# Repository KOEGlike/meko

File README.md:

> [!CAUTION]
> V3 is a WIP, if you want updates follow my [journal](JOURNAL.md). Check out the [v2 branch](https://github.com/KOEGlike/meko/tree/v2) for a completed project

# Meko

A linux music player with ddr3, a 70hz e-paper display and a haptic touchpad

## Components

- **_MPU_**: SAMA7D65, it can boost up to 1GHz, good audio subsystem and gpu
- **_RAM_**: Half a gig of DDR3L(MT41K256M16TW)
- **_EPD_**: Sharp MIP LS022B7DH03, can go up to 70Hz, 240x320
- **_Audio_**: TAC5212 
  - **_DAC+AMP_**: 192kHz, 32-bit, 120dB SNR, 2Vrms
  - **_ADC_**: 192kHz, 32-bit, 119dB SNR
- **_Wireless_**: Bluetooth 6 with LE audio and WiFi 6E
- **_Touchpad_**: IQS7211E touch IC with DRV2605 haptic LRA driver
- **_USB_**: USB 2.0 with OTG

## Shoutouts

- Diamond Master from The KiCAD discord: Thank you for doing sims! Without you doing the impedance sim the project would have failed!
- Cyao: Thank you for taking a deep look at my DDR routing and pointing out a **BUNCH** of issues! The performance of my DDR would have been cooked without you!
- Daniel from The KiCAD discord: Thank you for helping me with all the high-speed basics, and pointing out issues with my DDR!
- r/PrintedCircuitBoard: Thank you for pointing out a bunch of small and large mistakes both in my schematic and PCB
- Hack Club: Thank you for providing an awesome community and funding for my project!!
- All the other people from the KiCAD Discord! Y'all are awesome!!

## Journals

Each versions has a detailed journal:

[V3 journal](JOURNAL.md)

[V2 journal](JOURNAL_OLD_V2.md)

[V1 journal](JOURNAL_OLD_V1.md)

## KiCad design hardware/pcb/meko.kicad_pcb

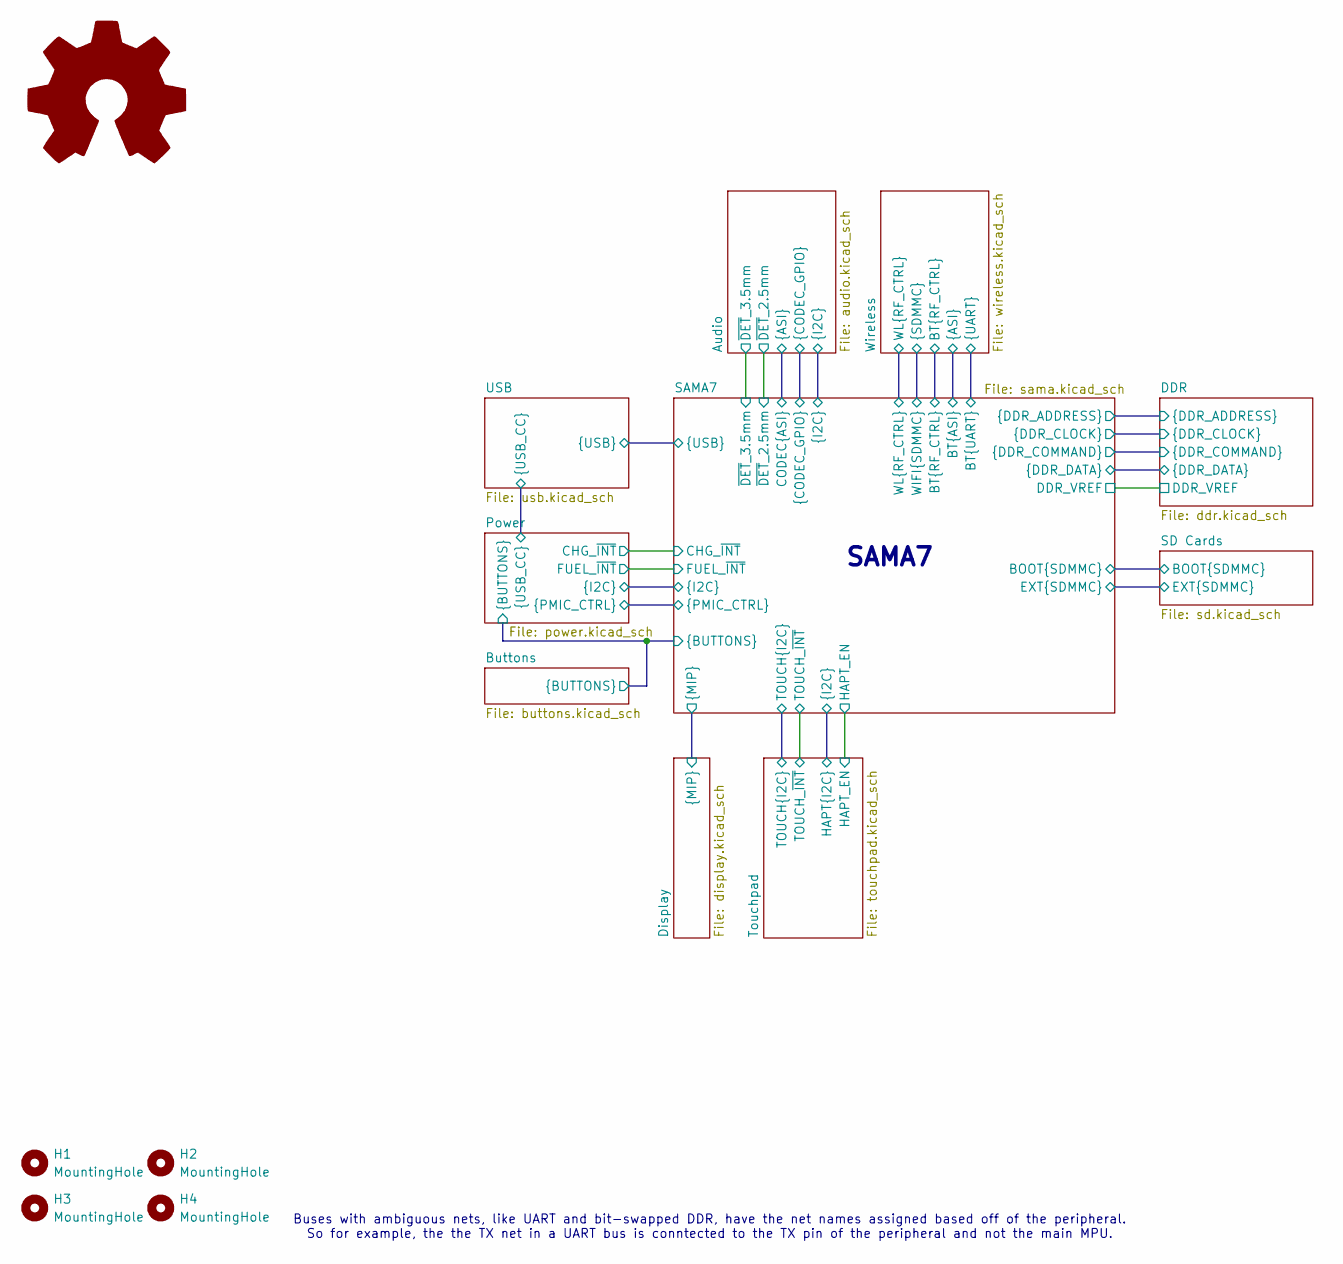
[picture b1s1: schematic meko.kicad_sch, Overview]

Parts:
H1, H2, H3, H4: MountingHole; MountingHole_2.2mm_M2
SYM1: Logo_Open_Hardware_Large; OSHW-Logo2_9.8x8mm_SilkScreen

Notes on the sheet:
Buses with ambiguous nets, like UART and bit-swapped DDR, have the net names assigned based off of the peripheral. So for example, the the TX net in a UART bus is conntected to the TX pin of the peripheral and not the main MPU.
SAMA7

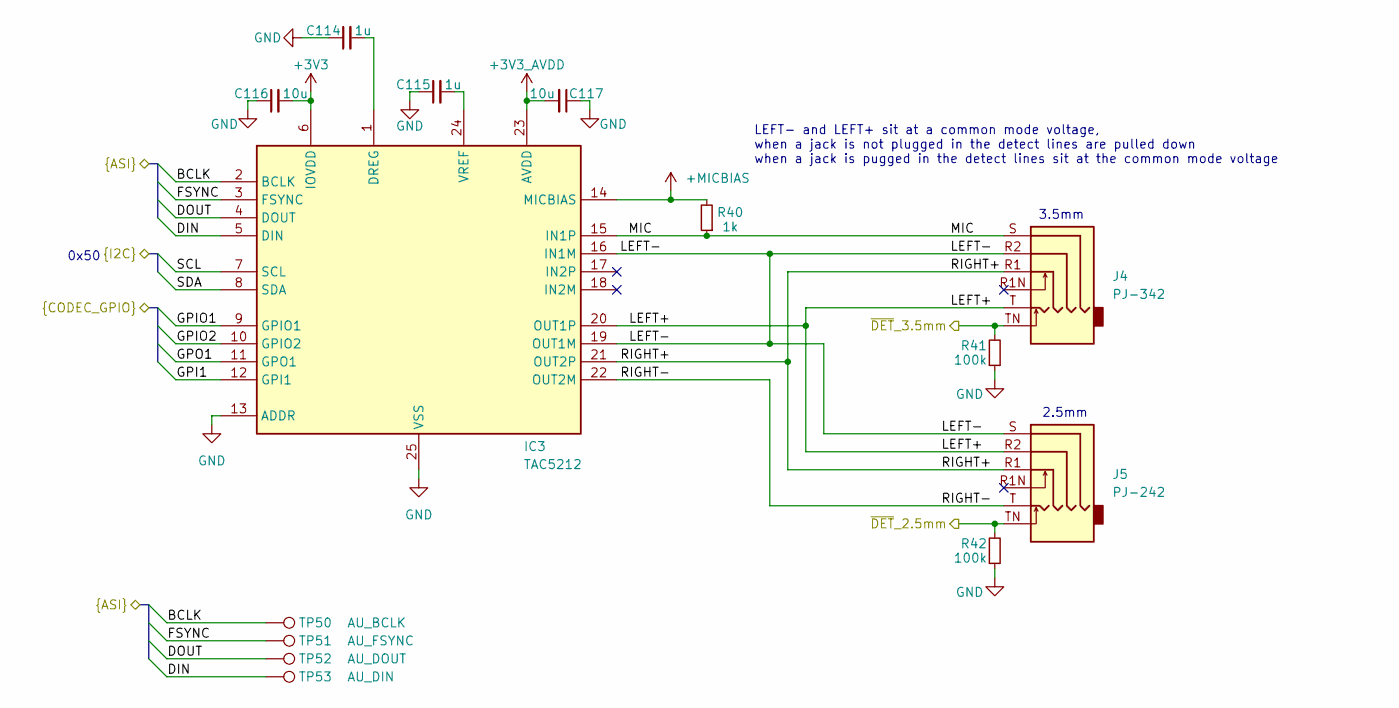
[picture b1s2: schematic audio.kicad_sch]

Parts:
C114, C115: 1u; C_0402_1005Metric
C116, C117: 10u; C_0402_1005Metric
IC3: TAC5212; VQFN-24-1EP_4x4mm_P0.5mm_EP2.45x2.45mm
J4: PJ-342; Jack_3.5mm_SHOUHAN_PJ-342; LCSC C668606
J5: PJ-242; Jack_2.5mm_PJ242_6P_12x6.2x4mm_Horizontal; LCSC C431536
R40: 1k; R_0402_1005Metric
R41, R42: 100k; R_0402_1005Metric
TP50: AU_BCLK; TestPoint_Pad_D1.0mm
TP51: AU_FSYNC; TestPoint_Pad_D1.0mm
TP52: AU_DOUT; TestPoint_Pad_D1.0mm
TP53: AU_DIN; TestPoint_Pad_D1.0mm

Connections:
+3V3: C116.2, IC3.6 (IOVDD); also elsewhere on the board
+3V3_AVDD: C117.2, IC3.23 (AVDD); also elsewhere on the board
+MICBIAS: IC3.14 (MICBIAS), R40.2
/Audio/BCLK: IC3.2 (BCLK), TP50.1 (1_1); also elsewhere on the board
/Audio/DIN: IC3.5 (DIN), TP53.1 (1_1); also elsewhere on the board
/Audio/DOUT: IC3.4 (DOUT), TP52.1 (1_1); also elsewhere on the board
/Audio/FSYNC: IC3.3 (FSYNC), TP51.1 (1_1); also elsewhere on the board
/Audio/GPI1: IC3.12 (GPI1); also elsewhere on the board
/Audio/GPIO1: IC3.9 (GPIO1); also elsewhere on the board
/Audio/GPIO2: IC3.10 (GPIO2); also elsewhere on the board
/Audio/GPO1: IC3.11 (GPO1); also elsewhere on the board
/Audio/LEFT+: IC3.20 (OUT1P), J4.T, J5.R2
/Audio/LEFT-: IC3.16 (IN1M), IC3.19 (OUT1M), J4.R2, J5.S
/Audio/MIC: IC3.15 (IN1P), J4.S, R40.1
/Audio/RIGHT+: IC3.21 (OUT2P), J4.R1, J5.R1
/Audio/RIGHT-: IC3.22 (OUT2M), J5.T
/Audio/SCL: IC3.7 (SCL); also elsewhere on the board
/Audio/SDA: IC3.8 (SDA); also elsewhere on the board
/Audio/~DET_2.5mm: J5.TN, R42.2; also elsewhere on the board
/Audio/~DET_3.5mm: J4.TN, R41.2; also elsewhere on the board
GND: C114.1, C115.1, C116.1, C117.1, IC3.13 (ADDR), IC3.25 (VSS), R41.1, R42.1; also elsewhere on the board
unnamed: C114.2, IC3.1 (DREG)
unnamed: C115.2, IC3.24 (VREF)

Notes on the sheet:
3.5mm
LEFT- and LEFT+ sit at a common mode voltage, when a jack is not plugged in the detect lines are pulled down when a jack is pugged in the detect lines sit at the common mode voltage
2.5mm
0x50

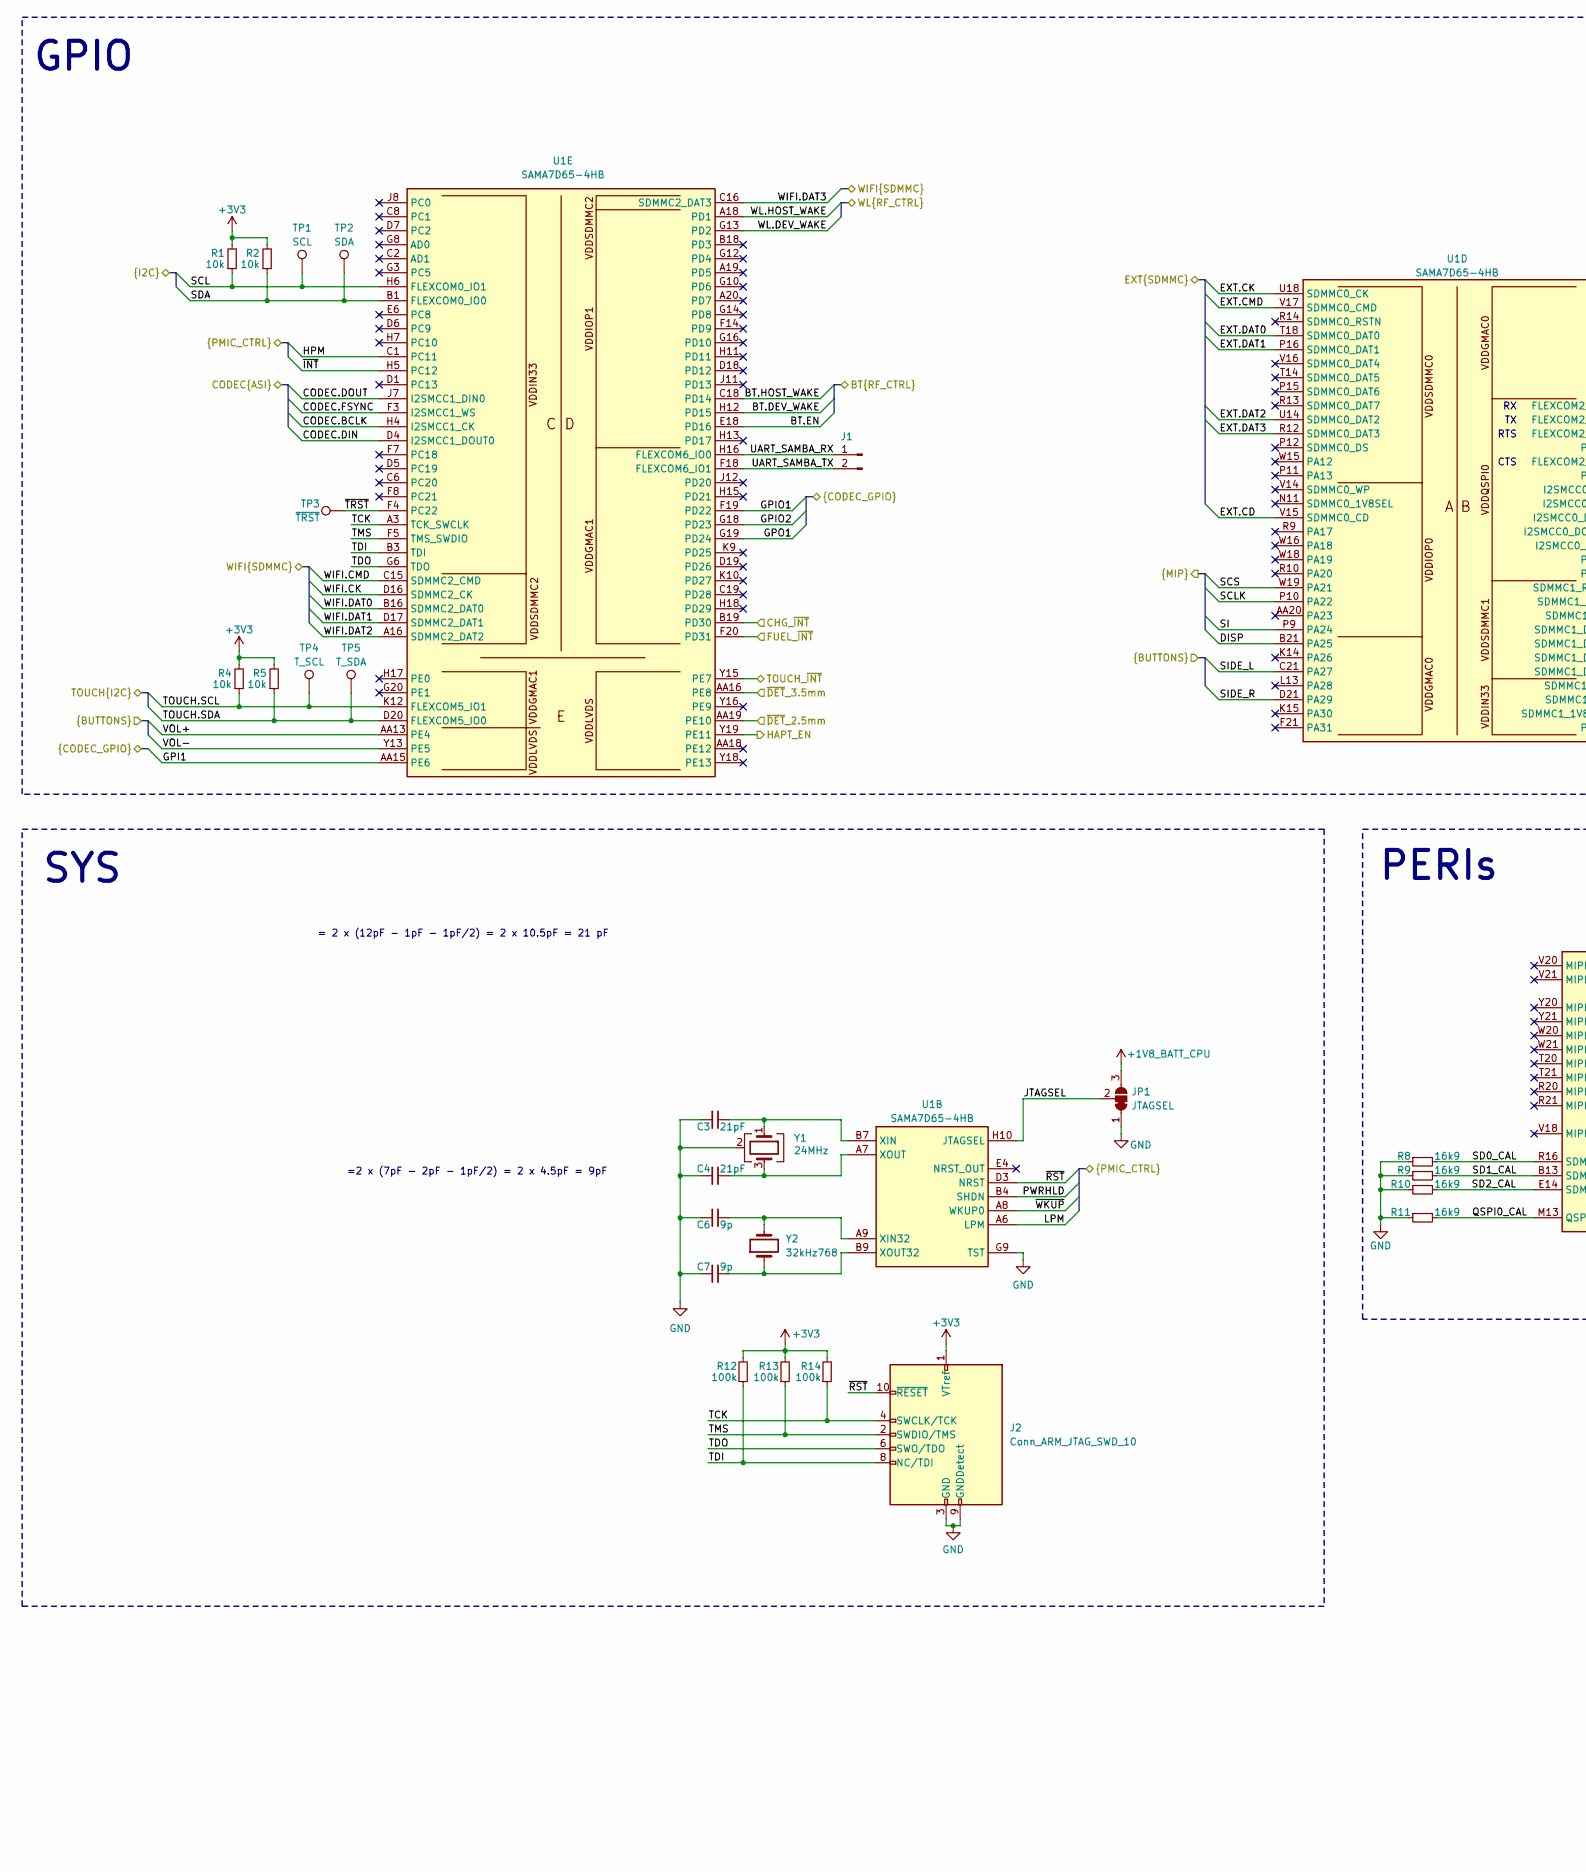
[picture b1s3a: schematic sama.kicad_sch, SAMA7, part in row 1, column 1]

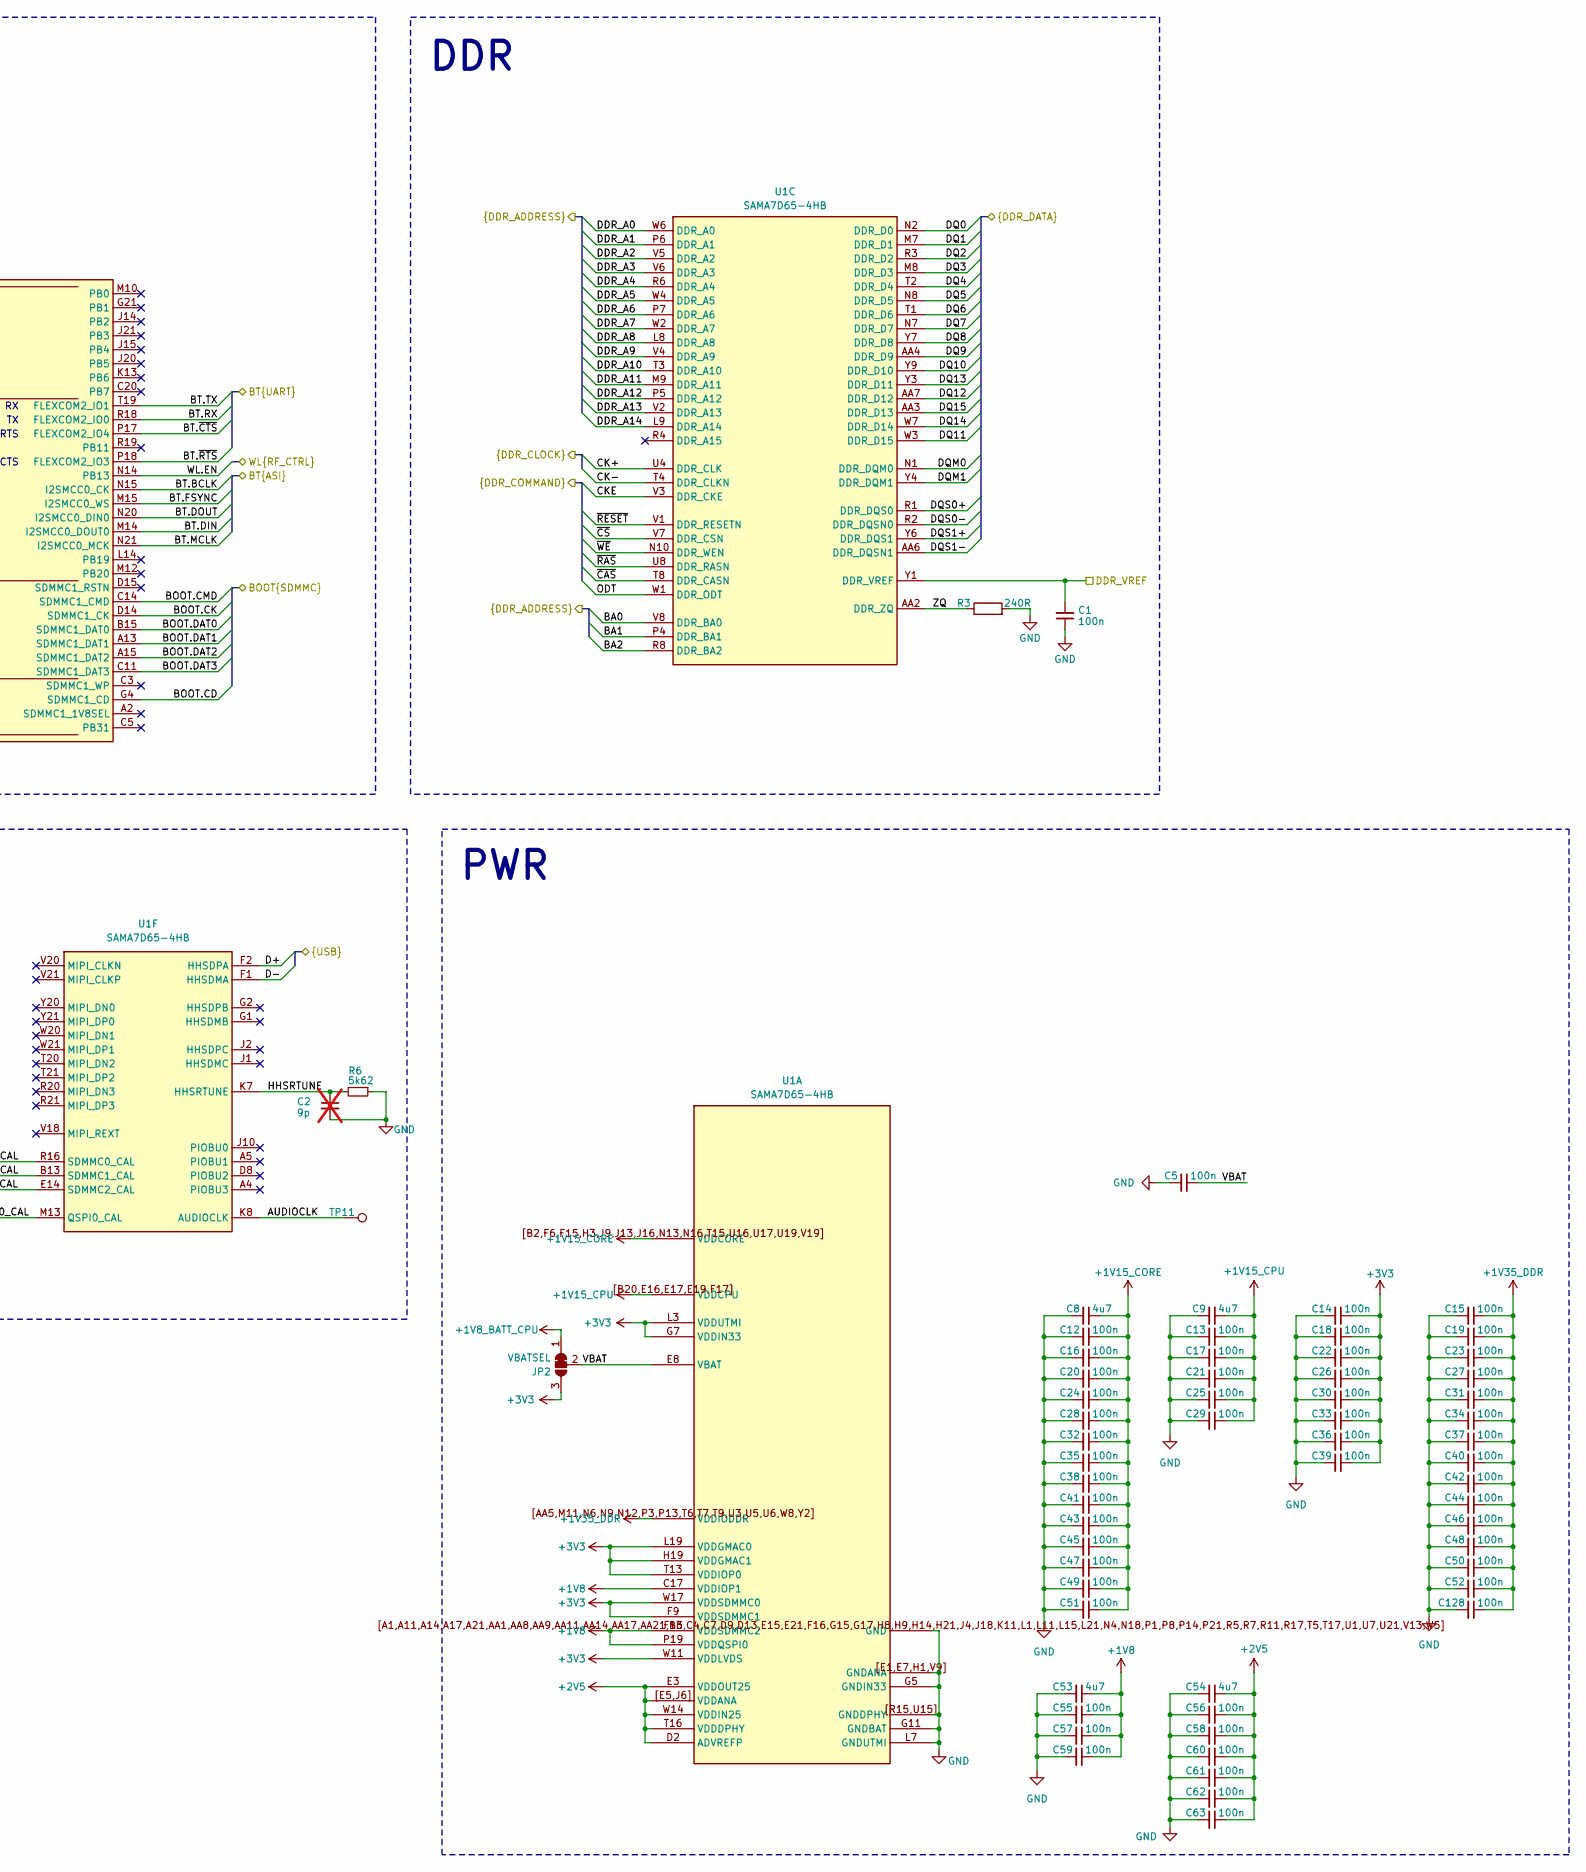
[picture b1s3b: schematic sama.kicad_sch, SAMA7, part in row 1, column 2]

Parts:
C1, C12, C15, C16, C18, C19, C20, C21, C22, C26, C28, C29, C30, C31, C39, C40, C43, C44, C46, C48, C51, C55, C56, C57, C59, C60, C62, C63, C128: 100n; C_0201_0603Metric
C2: 9p; C_0201_0603Metric; not fitted
C3, C4: 21pF; C_0201_0603Metric
C5, C13, C14, C17, C23, C24, C25, C27, C32, C33, C34, C35, C36, C37, C38, C41, C42, C45, C47, C49, C50, C52, C58, C61: 100n; C_0201_0603Metric_Dense
C6, C7: 9p; C_0201_0603Metric
C8, C9, C53, C54: 4u7; C_0402_1005Metric
J1: Conn_01x02_Pin; PinHeader_1x02_P2.54mm_Vertical
J2: Conn_ARM_JTAG_SWD_10; PinHeader_2x05_P1.27mm_Vertical
JP1: JTAGSEL; SolderJumper-3_P1.3mm_Bridged12_RoundedPad1.0x1.5mm
JP2: VBATSEL; SolderJumper-3_P1.3mm_Bridged12_RoundedPad1.0x1.5mm
R1, R2, R4, R5: 10k; R_0402_1005Metric
R3: 240R; R_0201_0603Metric
R6: 5k62; R_0201_0603Metric
R8, R9, R10, R11: 16k9; R_0201_0603Metric
R12, R13, R14: 100k; R_0402_1005Metric
TP1: SCL; TestPoint_Pad_D1.0mm
TP2: SDA; TestPoint_Pad_D1.0mm
TP3: ~{TRST}; TestPoint_Pad_D1.0mm
TP4: T_SCL; TestPoint_Pad_D1.0mm
TP5: T_SDA; TestPoint_Pad_D1.0mm
TP11: AUDIOCLK; TestPoint_Pad_D1.0mm
U1: SAMA7D65-4HB; Microchip_4HB_TFBGA-343_14x14mm_Layout21x21_P0.65mm
Y1: 24MHz; Crystal_SMD_3225-4Pin_3.2x2.5mm; MPN SX32Y024000BC1T001; LCSC C7420736
Y2: 32kHz768; Crystal_SMD_MicroCrystal_CC7V-T1A-2Pin_3.2x1.5mm; MPN SC-32S32.768kHz20PPM7pF

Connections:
+1V8: C53.1, C55.1, C57.1, C59.1, U1.C17 (VDDIOP1), U1.F13 (VDDSDMMC2), U1.P19 (VDDQSPI0); also elsewhere on the board
+1V8_BATT_CPU: JP1.3 (B), JP2.1 (A); also elsewhere on the board
+1V15_CORE: C8.1, C12.1, C16.1, C20.1, C24.1, C28.1, C32.1, C35.1, C38.1, C41.1, C43.1, C45.1, C47.1, C49.1, C51.1, U1.B2 (VDDCORE), U1.F6 (VDDCORE), U1.F15 (VDDCORE), U1.H3 (VDDCORE), U1.J9 (VDDCORE), U1.J13 (VDDCORE), U1.J16 (VDDCORE), U1.N13 (VDDCORE), U1.N16 (VDDCORE), U1.T15 (VDDCORE), U1.U16 (VDDCORE), U1.U17 (VDDCORE), U1.U19 (VDDCORE), U1.V19 (VDDCORE), U1.[B2,F6,F15,H3,J9,J1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 (VDDCORE); also elsewhere on the board
+1V15_CPU: C9.1, C13.1, C17.1, C21.1, C25.1, C29.1, U1.B20 (VDDCPU), U1.E16 (VDDCPU), U1.E17 (VDDCPU), U1.E19 (VDDCPU), U1.F17 (VDDCPU), U1.[B20,E16,E17,E19,F1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 (VDDCPU); also elsewhere on the board
+1V35_DDR: C15.1, C19.1, C23.1, C27.1, C31.1, C34.1, C37.1, C40.1, C42.1, C44.1, C46.1, C48.1, C50.1, C52.1, C128.1, U1.AA5 (VDDIODDR), U1.M11 (VDDIODDR), U1.N6 (VDDIODDR), U1.N9 (VDDIODDR), U1.N12 (VDDIODDR), U1.P3 (VDDIODDR), U1.P13 (VDDIODDR), U1.T6 (VDDIODDR), U1.T7 (VDDIODDR), U1.T9 (VDDIODDR), U1.U3 (VDDIODDR), U1.U5 (VDDIODDR), U1.U6 (VDDIODDR), U1.W8 (VDDIODDR), U1.Y2 (VDDIODDR), U1.[AA5,M11,N6,N9,N12,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 (VDDIODDR); also elsewhere on the board
+2V5: C54.1, C56.1, C58.1, C60.1, C61.1, C62.1, C63.1, U1.D2 (ADVREFP), U1.E3 (VDDOUT25), U1.E5 (VDDANA), U1.J6 (VDDANA), U1.T16 (VDDDPHY), U1.W14 (VDDIN25), U1.[E5,J6] (VDDANA)
+3V3: C14.1, C18.1, C22.1, C26.1, C30.1, C33.1, C36.1, C39.1, J2.1 (VTref), JP2.3 (B), R1.2, R2.2, R4.2, R5.2, R12.2, R13.2, R14.2, U1.F9 (VDDSDMMC1), U1.G7 (VDDIN33), U1.H19 (VDDGMAC1), U1.L3 (VDDUTMI), U1.L19 (VDDGMAC0), U1.T13 (VDDIOP0), U1.W11 (VDDLVDS), U1.W17 (VDDSDMMC0); also elsewhere on the board
/Audio/BCLK: U1.H4 (I2SMCC1_CK); also elsewhere on the board
/Audio/DIN: U1.D4 (I2SMCC1_DOUT0); also elsewhere on the board
/Audio/DOUT: U1.J7 (I2SMCC1_DIN0); also elsewhere on the board
/Audio/FSYNC: U1.F3 (I2SMCC1_WS); also elsewhere on the board
/Audio/GPI1: U1.AA15 (PE6); also elsewhere on the board
/Audio/GPIO1: U1.F19 (PD22); also elsewhere on the board
/Audio/GPIO2: U1.G18 (PD23); also elsewhere on the board
/Audio/GPO1: U1.G19 (PD24); also elsewhere on the board
/Audio/SCL: R1.1, TP1.1 (1_1), U1.H6 (FLEXCOM0_IO1); also elsewhere on the board
/Audio/SDA: R2.1, TP2.1 (1_1), U1.B1 (FLEXCOM0_IO0); also elsewhere on the board
/Audio/~DET_2.5mm: U1.AA19 (PE10); also elsewhere on the board
/Audio/~DET_3.5mm: U1.AA16 (PE8); also elsewhere on the board
/Buttons/SIDE_L: U1.C21 (PA27); also elsewhere on the board
/Buttons/SIDE_R: U1.D21 (PA29); also elsewhere on the board
/Buttons/VOL+: U1.AA13 (PE4); also elsewhere on the board
/Buttons/VOL-: U1.Y13 (PE5); also elsewhere on the board
/DDR/BA0: U1.V8 (DDR_BA0); also elsewhere on the board
/DDR/BA1: U1.P4 (DDR_BA1); also elsewhere on the board
/DDR/BA2: U1.R8 (DDR_BA2); also elsewhere on the board
/DDR/CK+: U1.U4 (DDR_CLK); also elsewhere on the board
/DDR/CK-: U1.T4 (DDR_CLKN); also elsewhere on the board
/DDR/CKE: U1.V3 (DDR_CKE); also elsewhere on the board
/DDR/DDR_A0: U1.W6 (DDR_A0); also elsewhere on the board
/DDR/DDR_A1: U1.P6 (DDR_A1); also elsewhere on the board
/DDR/DDR_A2: U1.V5 (DDR_A2); also elsewhere on the board
/DDR/DDR_A3: U1.V6 (DDR_A3); also elsewhere on the board
/DDR/DDR_A4: U1.R6 (DDR_A4); also elsewhere on the board
/DDR/DDR_A5: U1.W4 (DDR_A5); also elsewhere on the board
/DDR/DDR_A6: U1.P7 (DDR_A6); also elsewhere on the board
/DDR/DDR_A7: U1.W2 (DDR_A7); also elsewhere on the board
/DDR/DDR_A8: U1.L8 (DDR_A8); also elsewhere on the board
/DDR/DDR_A9: U1.V4 (DDR_A9); also elsewhere on the board
/DDR/DDR_A10: U1.T3 (DDR_A10); also elsewhere on the board
/DDR/DDR_A11: U1.M9 (DDR_A11); also elsewhere on the board
/DDR/DDR_A12: U1.P5 (DDR_A12); also elsewhere on the board
/DDR/DDR_A13: U1.V2 (DDR_A13); also elsewhere on the board
/DDR/DDR_A14: U1.L9 (DDR_A14); also elsewhere on the board
/DDR/DDR_VREF: C1.2, U1.Y1 (DDR_VREF); also elsewhere on the board
/DDR/DQ0: U1.N2 (DDR_D0); also elsewhere on the board
/DDR/DQ1: U1.M7 (DDR_D1); also elsewhere on the board
/DDR/DQ2: U1.R3 (DDR_D2); also elsewhere on the board
/DDR/DQ3: U1.M8 (DDR_D3); also elsewhere on the board
/DDR/DQ4: U1.T2 (DDR_D4); also elsewhere on the board
/DDR/DQ5: U1.N8 (DDR_D5); also elsewhere on the board
/DDR/DQ6: U1.T1 (DDR_D6); also elsewhere on the board
/DDR/DQ7: U1.N7 (DDR_D7); also elsewhere on the board
/DDR/DQ8: U1.Y7 (DDR_D8); also elsewhere on the board
/DDR/DQ9: U1.AA4 (DDR_D9); also elsewhere on the board
/DDR/DQ10: U1.Y9 (DDR_D10); also elsewhere on the board
/DDR/DQ11: U1.W3 (DDR_D15); also elsewhere on the board
/DDR/DQ12: U1.AA7 (DDR_D12); also elsewhere on the board
/DDR/DQ13: U1.Y3 (DDR_D11); also elsewhere on the board
/DDR/DQ14: U1.W7 (DDR_D14); also elsewhere on the board
/DDR/DQ15: U1.AA3 (DDR_D13); also elsewhere on the board
/DDR/DQM0: U1.N1 (DDR_DQM0); also elsewhere on the board
/DDR/DQM1: U1.Y4 (DDR_DQM1); also elsewhere on the board
/DDR/DQS0+: U1.R1 (DDR_DQS0); also elsewhere on the board
/DDR/DQS0-: U1.R2 (DDR_DQSN0); also elsewhere on the board
/DDR/DQS1+: U1.Y6 (DDR_DQS1); also elsewhere on the board
/DDR/DQS1-: U1.AA6 (DDR_DQSN1); also elsewhere on the board
/DDR/ODT: U1.W1 (DDR_ODT); also elsewhere on the board
/DDR/~CAS: U1.T8 (DDR_CASN); also elsewhere on the board
/DDR/~CS: U1.V7 (DDR_CSN); also elsewhere on the board
/DDR/~RAS: U1.U8 (DDR_RASN); also elsewhere on the board
/DDR/~RESET: U1.V1 (DDR_RESETN); also elsewhere on the board
/DDR/~WE: U1.N10 (DDR_WEN); also elsewhere on the board
/Display/DISP: U1.B21 (PA25); also elsewhere on the board
/Display/SCLK: U1.P10 (PA22); also elsewhere on the board
/Display/SCS: U1.W19 (PA21); also elsewhere on the board
/Display/SI: U1.P9 (PA24); also elsewhere on the board
/Power/CHG_~INT: U1.B19 (PD30); also elsewhere on the board
/Power/FUEL_~INT: U1.F20 (PD31); also elsewhere on the board
/Power/HPM: U1.C1 (PC11); also elsewhere on the board
/Power/LPM: U1.A6 (LPM); also elsewhere on the board
/Power/PWRHLD: U1.B4 (SHDN); also elsewhere on the board
/Power/~INT: U1.H5 (PC12); also elsewhere on the board
/Power/~RST: J2.10 (~RESET), U1.D3 (NRST); also elsewhere on the board
/Power/~WKUP: U1.A8 (WKUP0); also elsewhere on the board
/SAMA7/AUDIOCLK: TP11.1 (1_1), U1.K8 (AUDIOCLK)
/SAMA7/BOOT.CD: U1.G4 (SDMMC1_CD); also elsewhere on the board
/SAMA7/BOOT.CK: U1.D14 (SDMMC1_CK); also elsewhere on the board
/SAMA7/BOOT.CMD: U1.C14 (SDMMC1_CMD); also elsewhere on the board
/SAMA7/BOOT.DAT0: U1.B15 (SDMMC1_DAT0); also elsewhere on the board
/SAMA7/BOOT.DAT1: U1.A13 (SDMMC1_DAT1); also elsewhere on the board
/SAMA7/BOOT.DAT2: U1.A15 (SDMMC1_DAT2); also elsewhere on the board
/SAMA7/BOOT.DAT3: U1.C11 (SDMMC1_DAT3); also elsewhere on the board
/SAMA7/BT.BCLK: U1.N15 (I2SMCC0_CK); also elsewhere on the board
/SAMA7/BT.DEV_WAKE: U1.H12 (PD15); also elsewhere on the board
/SAMA7/BT.DIN: U1.M14 (I2SMCC0_DOUT0); also elsewhere on the board
/SAMA7/BT.DOUT: U1.N20 (I2SMCC0_DIN0); also elsewhere on the board
/SAMA7/BT.EN: U1.E18 (PD16); also elsewhere on the board
/SAMA7/BT.FSYNC: U1.M15 (I2SMCC0_WS); also elsewhere on the board
/SAMA7/BT.HOST_WAKE: U1.C18 (PD14); also elsewhere on the board
/SAMA7/BT.MCLK: U1.N21 (I2SMCC0_MCK); also elsewhere on the board
/SAMA7/BT.RX: U1.R18 (FLEXCOM2_IO0); also elsewhere on the board
/SAMA7/BT.TX: U1.T19 (FLEXCOM2_IO1); also elsewhere on the board
/SAMA7/BT.~CTS: U1.P17 (FLEXCOM2_IO4); also elsewhere on the board
/SAMA7/BT.~RTS: U1.P18 (FLEXCOM2_IO3); also elsewhere on the board
/SAMA7/D+: U1.F2 (HHSDPA); also elsewhere on the board
/SAMA7/D-: U1.F1 (HHSDMA); also elsewhere on the board
/SAMA7/EXT.CD: U1.V15 (SDMMC0_CD); also elsewhere on the board
/SAMA7/EXT.CK: U1.U18 (SDMMC0_CK); also elsewhere on the board
/SAMA7/EXT.CMD: U1.V17 (SDMMC0_CMD); also elsewhere on the board
/SAMA7/EXT.DAT0: U1.T18 (SDMMC0_DAT0); also elsewhere on the board
/SAMA7/EXT.DAT1: U1.P16 (SDMMC0_DAT1); also elsewhere on the board
/SAMA7/EXT.DAT2: U1.U14 (SDMMC0_DAT2); also elsewhere on the board
/SAMA7/EXT.DAT3: U1.R12 (SDMMC0_DAT3); also elsewhere on the board
/SAMA7/HAPT_EN: U1.Y19 (PE11); also elsewhere on the board
/SAMA7/HHSRTUNE: C2.1, R6.2, U1.K7 (HHSRTUNE)
/SAMA7/JTAGSEL: JP1.2 (C), U1.H10 (JTAGSEL)
/SAMA7/QSPI0_CAL: R11.2, U1.M13 (QSPI0_CAL)
/SAMA7/SD0_CAL: R8.2, U1.R16 (SDMMC0_CAL)
/SAMA7/SD1_CAL: R9.2, U1.B13 (SDMMC1_CAL)
/SAMA7/SD2_CAL: R10.2, U1.E14 (SDMMC2_CAL)
/SAMA7/TCK: J2.4 (SWCLK/TCK), R14.1, U1.A3 (TCK_SWCLK)
/SAMA7/TDI: J2.8 (NC/TDI), R12.1, U1.B3 (TDI)
/SAMA7/TDO: J2.6 (SWO/TDO), U1.G6 (TDO)
/SAMA7/TMS: J2.2 (SWDIO/TMS), R13.1, U1.F5 (TMS_SWDIO)
/SAMA7/TOUCH.SCL: R4.1, TP4.1 (1_1), U1.K12 (FLEXCOM5_IO1); also elsewhere on the board
/SAMA7/TOUCH.SDA: R5.1, TP5.1 (1_1), U1.D20 (FLEXCOM5_IO0); also elsewhere on the board
/SAMA7/TOUCH_~INT: U1.Y15 (PE7); also elsewhere on the board
/SAMA7/UART_SAMBA_RX: J1.1, U1.H16 (FLEXCOM6_IO0)
/SAMA7/UART_SAMBA_TX: J1.2, U1.F18 (FLEXCOM6_IO1)
/SAMA7/VBAT: C5.1, JP2.2 (C), U1.E8 (VBAT)
/SAMA7/WIFI.CK: U1.D16 (SDMMC2_CK); also elsewhere on the board
/SAMA7/WIFI.CMD: U1.C15 (SDMMC2_CMD); also elsewhere on the board
/SAMA7/WIFI.DAT0: U1.B16 (SDMMC2_DAT0); also elsewhere on the board
/SAMA7/WIFI.DAT1: U1.D17 (SDMMC2_DAT1); also elsewhere on the board
/SAMA7/WIFI.DAT2: U1.A16 (SDMMC2_DAT2); also elsewhere on the board
/SAMA7/WIFI.DAT3: U1.C16 (SDMMC2_DAT3); also elsewhere on the board
/SAMA7/WL.DEV_WAKE: U1.G13 (PD2); also elsewhere on the board
/SAMA7/WL.EN: U1.N14 (PB13); also elsewhere on the board
/SAMA7/WL.HOST_WAKE: U1.A18 (PD1); also elsewhere on the board
/SAMA7/ZQ: R3.1, U1.AA2 (DDR_ZQ)
/SAMA7/~TRST: TP3.1 (1_1), U1.F4 (PC22)
GND: C1.1, C2.2, C3.2, C4.2, C5.2, C6.2, C7.2, C8.2, C9.2, C12.2, C13.2, C14.2, C15.2, C16.2, C17.2, C18.2, C19.2, C20.2, C21.2, C22.2, C23.2, C24.2, C25.2, C26.2, C27.2, C28.2, C29.2, C30.2, C31.2, C32.2, C33.2, C34.2, C35.2, C36.2, C37.2, C38.2, C39.2, C40.2, C41.2, C42.2, C43.2, C44.2, C45.2, C46.2, C47.2, C48.2, C49.2, C50.2, C51.2, C52.2, C53.2, C54.2, C55.2, C56.2, C57.2, C58.2, C59.2, C60.2, C61.2, C62.2, C63.2, C128.2, J2.3 (GND), J2.5 (GND), J2.9 (GNDDetect), JP1.1 (A), R3.2, R6.1, R8.1, R9.1, R10.1, R11.1, U1.A1 (GND), U1.A11 (GND), U1.A14 (GND), U1.A17 (GND), U1.A21 (GND), U1.AA1 (GND), U1.AA8 (GND), U1.AA9 (GND), U1.AA11 (GND), U1.AA14 (GND), U1.AA17 (GND), U1.AA21 (GND), U1.B6 (GND), U1.C4 (GND), U1.C7 (GND), U1.D9 (GND), U1.D13 (GND), U1.E1 (GNDANA), U1.E7 (GNDANA), U1.E15 (GND), U1.E21 (GND), U1.F16 (GND), U1.G5 (GNDIN33), U1.G9 (TST), U1.G11 (GNDBAT), U1.G15 (GND), U1.G17 (GND), U1.H1 (GNDANA), U1.H8 (GND), U1.H9 (GND), U1.H14 (GND), U1.H21 (GND), U1.J4 (GND), U1.J18 (GND), U1.K11 (GND), U1.L1 (GND), U1.L7 (GNDUTMI), U1.L11 (GND), U1.L15 (GND), U1.L21 (GND), U1.N4 (GND), U1.N18 (GND), U1.P1 (GND), U1.P8 (GND), U1.P14 (GND), U1.P21 (GND), U1.R5 (GND), U1.R7 (GND), U1.R11 (GND), U1.R15 (GNDDPHY), U1.R17 (GND), U1.T5 (GND), U1.T17 (GND), U1.U1 (GND), U1.U7 (GND), U1.U15 (GNDDPHY), U1.U21 (GND), U1.V9 (GNDANA), U1.V13 (GND), U1.W5 (GND), U1.[A1,A11,A14,A17,A21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 (GND), U1.[E1,E7,H1,V9] (GNDANA), U1.[R15,U15] (GNDDPHY), Y1.2 (G), Y1.4 (G); also elsewhere on the board
unnamed: C6.1, U1.A9 (XIN32), Y2.2
unnamed: C3.1, U1.B7 (XIN), Y1.1
unnamed: C7.1, U1.B9 (XOUT32), Y2.1
unnamed: C4.1, U1.A7 (XOUT), Y1.3

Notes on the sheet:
PERIs
GPIO
=2 x (7pF - 2pF - 1pF/2) = 2 x 4.5pF = 9pF
= 2 x (12pF - 1pF - 1pF/2) = 2 x 10.5pF = 21 pF
SYS
PWR
DDR
CTS
RTS

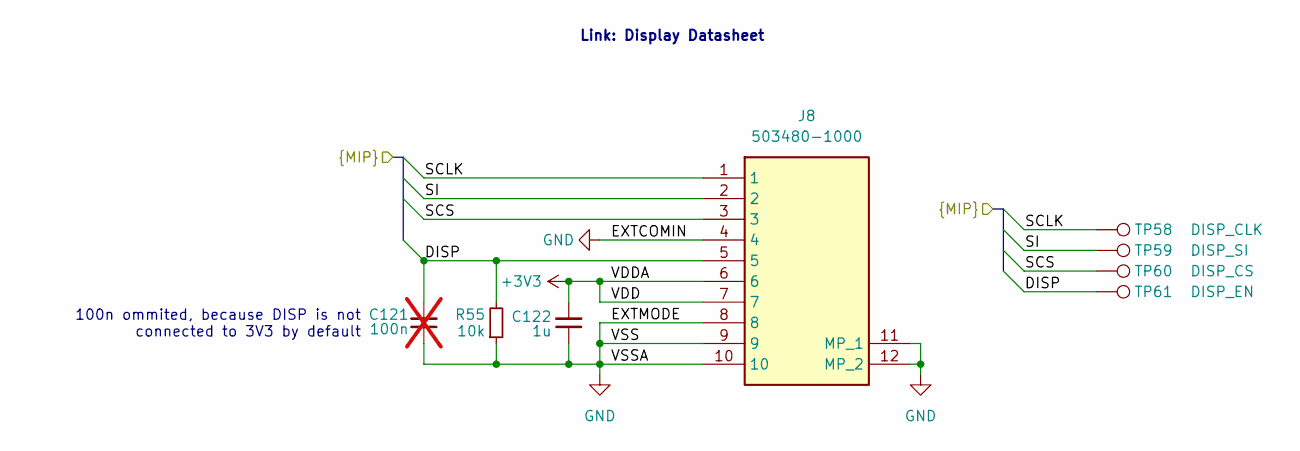
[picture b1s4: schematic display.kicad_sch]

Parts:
C121: 100n; C_0201_0603Metric; not fitted
C122: 1u; C_0402_1005Metric
J8: 503480-1000; 5034801000; MPN 503480-1000; LCSC C127355
R55: 10k; R_0402_1005Metric
TP58: DISP_CLK; TestPoint_Pad_D1.0mm
TP59: DISP_SI; TestPoint_Pad_D1.0mm
TP60: DISP_CS; TestPoint_Pad_D1.0mm
TP61: DISP_EN; TestPoint_Pad_D1.0mm

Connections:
+3V3: C122.2, J8.6, J8.7; also elsewhere on the board
/Display/DISP: C121.2, J8.5, R55.2, TP61.1 (1_1); also elsewhere on the board
/Display/SCLK: J8.1, TP58.1 (1_1); also elsewhere on the board
/Display/SCS: J8.3, TP60.1 (1_1); also elsewhere on the board
/Display/SI: J8.2, TP59.1 (1_1); also elsewhere on the board
GND: C121.1, C122.1, J8.4, J8.8, J8.9, J8.10, J8.11 (MP_1), J8.12 (MP_2), R55.1; also elsewhere on the board

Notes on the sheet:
100n ommited, because DISP is not connected to 3V3 by default
Link: Display Datasheet

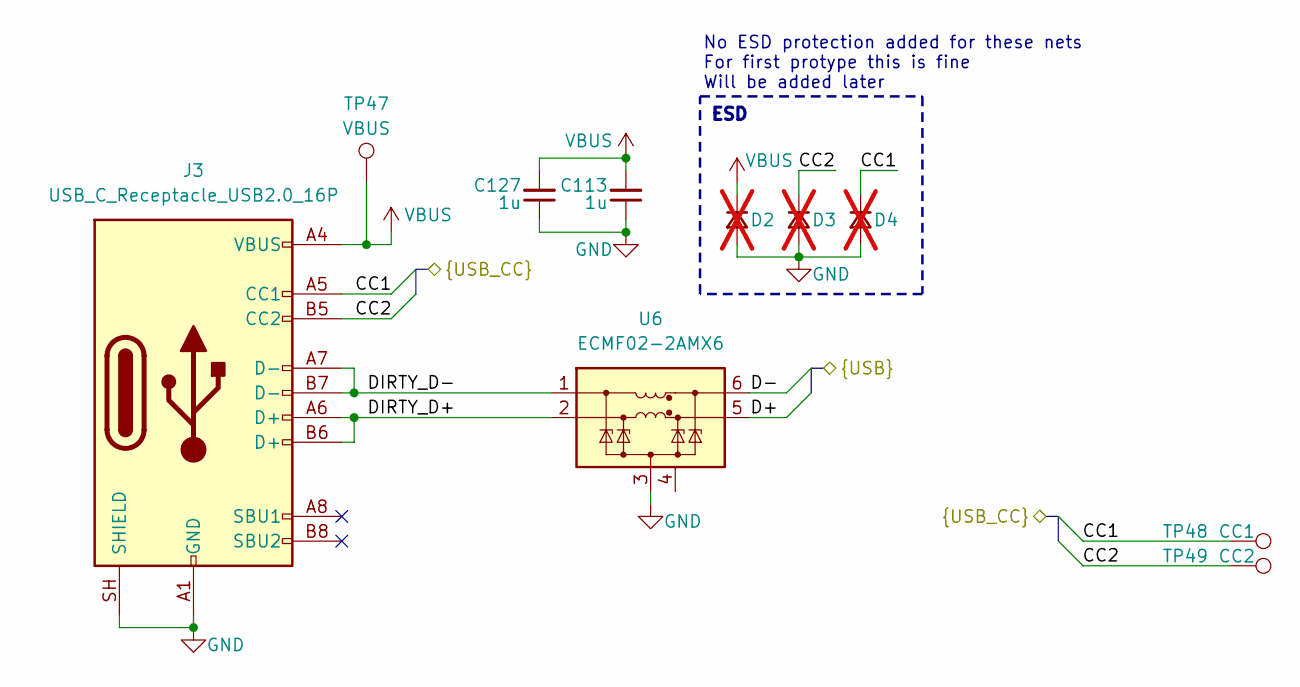
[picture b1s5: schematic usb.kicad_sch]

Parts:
C113, C127: 1u; C_0402_1005Metric
D2, D3, D4: ESD441; ESD441DPLR; not fitted
J3: USB_C_Receptacle_USB2.0_16P; USB_C_Receptacle_HRO_TYPE-C-31-M-12
TP47: VBUS; TestPoint_Pad_D1.0mm
TP48: CC1; TestPoint_Pad_D1.0mm
TP49: CC2; TestPoint_Pad_D1.0mm
U6: ECMF02-2AMX6; ST_UQFN-6L_1.5x1.7mm_P0.5mm

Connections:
/Power/CC1: D4.1 (K), J3.A5 (CC1), TP48.1 (1_1); also elsewhere on the board
/Power/CC2: D3.1 (K), J3.B5 (CC2), TP49.1 (1_1); also elsewhere on the board
/SAMA7/D+: U6.5 (D-_out); also elsewhere on the board
/SAMA7/D-: U6.6 (D+_out); also elsewhere on the board
/USB/DIRTY_D+: J3.A6 (D+), J3.B6 (D+), U6.2 (D-_in)
/USB/DIRTY_D-: J3.A7 (D-), J3.B7 (D-), U6.1 (D+_in)
GND: C113.1, C127.1, D2.2 (A), D3.2 (A), D4.2 (A), J3.A1 (GND), J3.A12 (GND), J3.B1 (GND), J3.B12 (GND), J3.SH (SHIELD), U6.3 (GND); also elsewhere on the board
VBUS: C113.2, C127.2, D2.1 (K), J3.A4 (VBUS), J3.A9 (VBUS), J3.B4 (VBUS), J3.B9 (VBUS), TP47.1 (1_1); also elsewhere on the board

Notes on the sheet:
No ESD protection added for these nets For first protype this is fine Will be added later
ESD

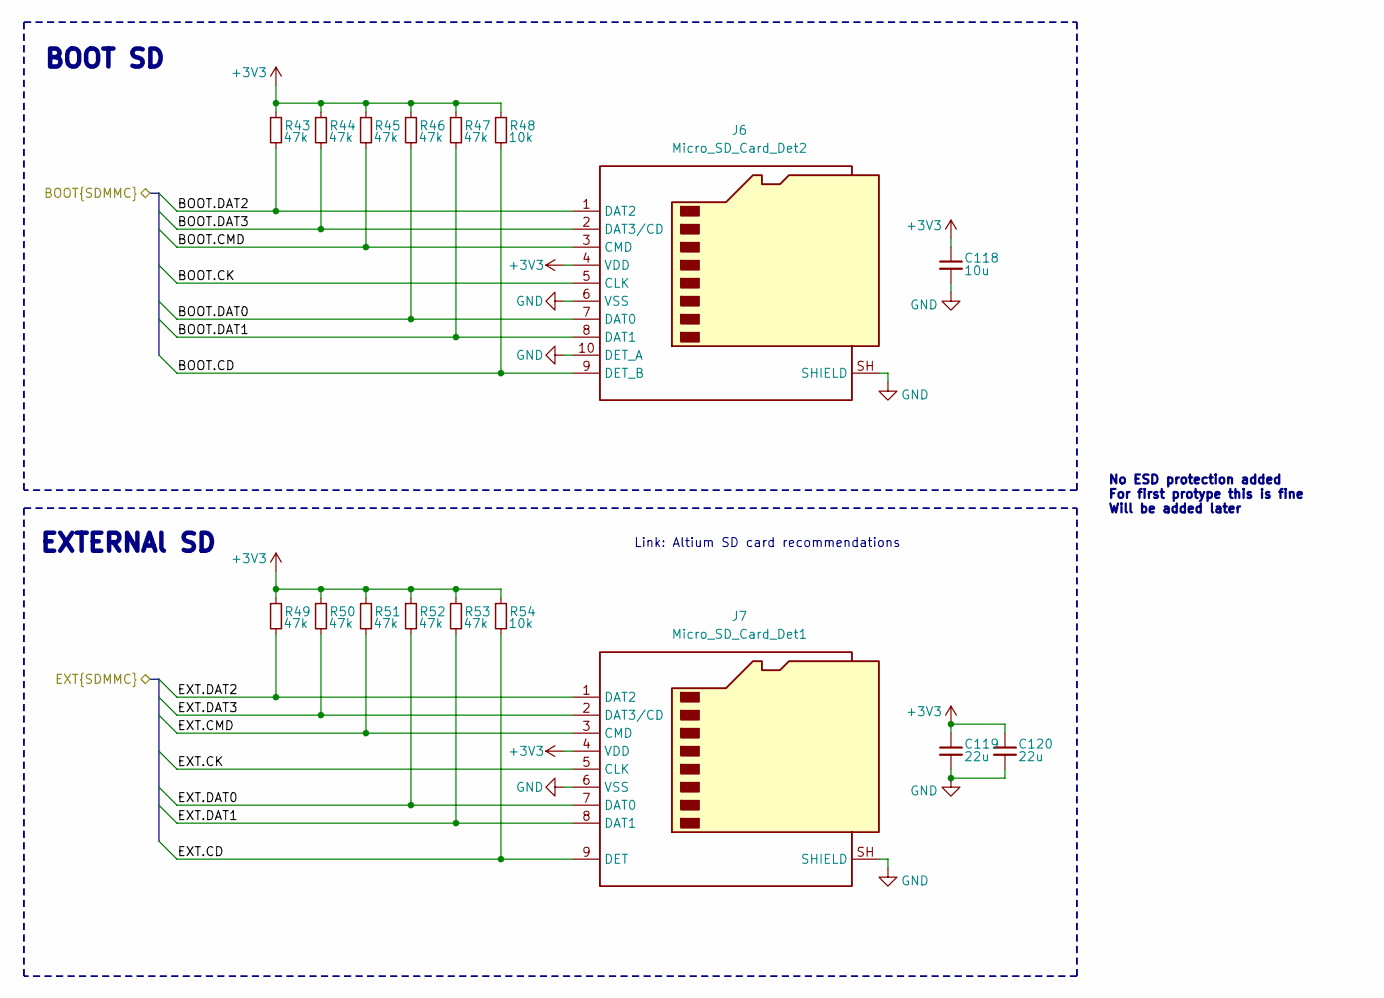
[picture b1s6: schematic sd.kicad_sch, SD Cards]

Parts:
C118: 10u; C_0402_1005Metric
C119, C120: 22u; C_0603_1608Metric
J6: Micro_SD_Card_Det2; microSD_SOFNG_TF-008; MPN TF-008; LCSC C428465
J7: Micro_SD_Card_Det1; microSD_XYECONN_TF-015-ZYD9AH185; MPN TF-015-ZYD9AH1.85; LCSC C20613194
R43, R44, R45, R46, R47, R49, R50, R51, R52, R53: 47k; R_0402_1005Metric
R48, R54: 10k; R_0402_1005Metric

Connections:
+3V3: C118.1, C119.1, C120.1, J6.4 (VDD), J7.4 (VDD), R43.1, R44.1, R45.1, R46.1, R47.1, R48.1, R49.1, R50.1, R51.1, R52.1, R53.1, R54.1; also elsewhere on the board
/SAMA7/BOOT.CD: J6.9 (DET_B), R48.2; also elsewhere on the board
/SAMA7/BOOT.CK: J6.5 (CLK); also elsewhere on the board
/SAMA7/BOOT.CMD: J6.3 (CMD), R45.2; also elsewhere on the board
/SAMA7/BOOT.DAT0: J6.7 (DAT0), R46.2; also elsewhere on the board
/SAMA7/BOOT.DAT1: J6.8 (DAT1), R47.2; also elsewhere on the board
/SAMA7/BOOT.DAT2: J6.1 (DAT2), R43.2; also elsewhere on the board
/SAMA7/BOOT.DAT3: J6.2 (DAT3/CD), R44.2; also elsewhere on the board
/SAMA7/EXT.CD: J7.9 (DET), R54.2; also elsewhere on the board
/SAMA7/EXT.CK: J7.5 (CLK); also elsewhere on the board
/SAMA7/EXT.CMD: J7.3 (CMD), R51.2; also elsewhere on the board
/SAMA7/EXT.DAT0: J7.7 (DAT0), R52.2; also elsewhere on the board
/SAMA7/EXT.DAT1: J7.8 (DAT1), R53.2; also elsewhere on the board
/SAMA7/EXT.DAT2: J7.1 (DAT2), R49.2; also elsewhere on the board
/SAMA7/EXT.DAT3: J7.2 (DAT3/CD), R50.2; also elsewhere on the board
GND: C118.2, C119.2, C120.2, J6.6 (VSS), J6.10 (DET_A), J6.SH (SHIELD), J7.6 (VSS), J7.SH (SHIELD); also elsewhere on the board

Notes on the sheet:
EXTERNAl SD
No ESD protection added For first protype this is fine Will be added later
Link: Altium SD card recommendations
BOOT SD
